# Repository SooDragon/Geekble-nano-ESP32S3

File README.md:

Geekble nano ESP32-S3
=============
Geekble nano ESP32-S3 문서에 오신것을 환영합니다

아두이노 IDE에서 쉽게 사용할 수 있는 Geekble nano를 통해 WiFi, Bluetooth, USB HID 기능을 여러분의 프로젝트에 구현할 수 있습니다

Geekble nano 핀맵
-------------

Geekble nano PinMap

Geekble nano 회로도
-------------

Geekble nano Schematic

Geekble nano 치수도
-------------

Geekble nano Dimension

Geekble nano Version Log
-------------
- Ver.1.0: 최초 공개 버전
- Ver.2.0: 3.3V Buck-Boost 회로에서 5V Buck-Boost + 3.3V 리니어 레귤레이터 구조로 변경
- Ver.2.2: 안테나 임피던스 매칭용 커페시터 C1, C2 값을 1.8pF에서 1.5pF으로 변경
- Ver.2.3: 안테나 임피던스 매칭용 커페시터 C1 값을 2pF으로, C2 값을 1pF으로 변경
- Ver.2.4:안테나 임피던스 매칭용 커페시터 C1 값을 1pF으로, C2 값을 2pF으로 변경
- Ver.2.5: 안테나 임피던스 매칭용 커페시터 C1 값을 1pF에서 1.2pF으로 변경

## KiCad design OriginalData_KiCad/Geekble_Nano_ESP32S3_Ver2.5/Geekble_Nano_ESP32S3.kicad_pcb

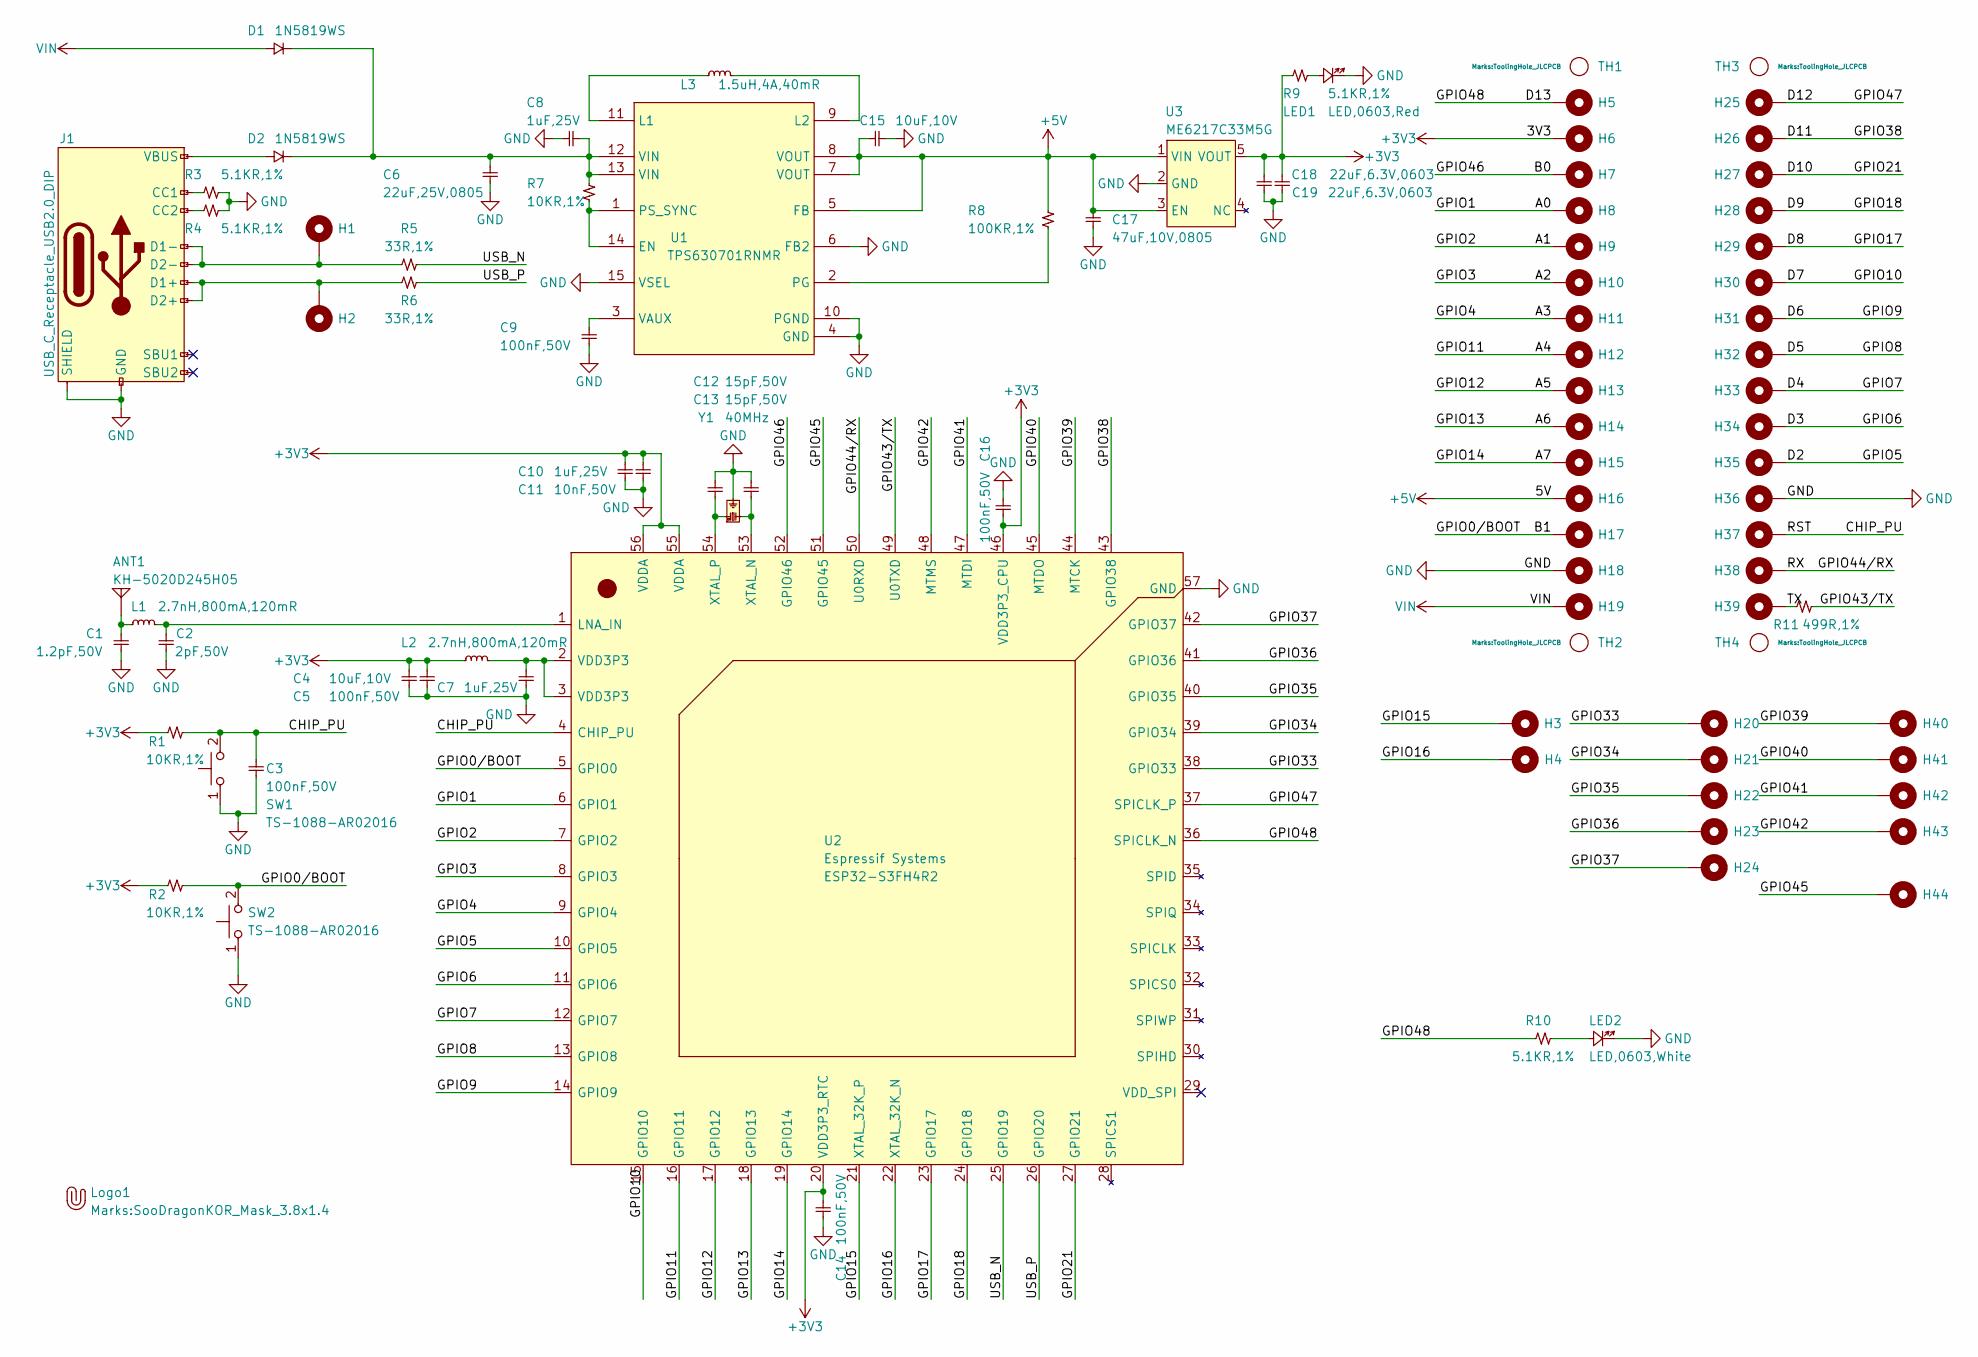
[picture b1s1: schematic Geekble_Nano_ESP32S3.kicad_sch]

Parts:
ANT1: KH-5020D245H05; ANT_5020; Manufacturer Part Number KH-5020D245H05; LCSC C45359218
C1: 1.2pF,50V; C_0402; Manufacturer Part Number CC0402BRNPO9BN1R2; LCSC C327292
C2: 2pF,50V; C_0402; Manufacturer Part Number CC0402BRNPO9BN2R0; LCSC C281756
C3, C5, C9, C14, C16: 100nF,50V; C_0402; Manufacturer Part Number CL05B104KB54PNC; LCSC C307331
C4, C15: 10uF,10V; C_0402; Manufacturer Part Number LDK105CBJ106MVLF; LCSC C386033
C6: 22uF,25V,0805; C_0805; Manufacturer Part Number CL21A226MAQNNNE; LCSC C45783
C7, C8, C10: 1uF,25V; C_0402; Manufacturer Part Number CL05A105KA5NQNC; LCSC C52923
C11: 10nF,50V; C_0402; Manufacturer Part Number CL05B103KB5NNNC; LCSC C15195
C12, C13: 15pF,50V; C_0402; Manufacturer Part Number 0402CG150J500NT; LCSC C1548
C17: 47uF,10V,0805; C_0805; Manufacturer Part Number GRM21BR61A476ME15L; LCSC C124129
C18, C19: 22uF,6.3V,0603; C_0603; Manufacturer Part Number CL10A226MQ8NRNC; LCSC C59461
D1, D2: 1N5819WS; SOD-323F; Manufacturer Part Number 1N5819WS; LCSC C191023
H1, H2, H3, H4, H20, H21, H22, H23, H24, H40, H41, H42, H43, H44: MountingHole_Pad; 1x1_1.0piPad_SMD
H5, H6, H7, H8, H9, H10, H11, H12, H13, H14, H15, H16, H17, H18, H19, H25, H26, H27, H28, H29, H30, H31, H32, H33, H34, H35, H36, H37, H38, H39: MountingHole_Pad; 1x1_P2.54_CastellatedPad
J1: USB_C_Receptacle_USB2.0_DIP; USB_DIP,8.94x7.3mm; Manufacturer Part Number TYPE-C-31-M-12; LCSC C165948
L1, L2: 2.7nH,800mA,120mR; L_0402; Manufacturer Part Number LQG15HS2N7S02D; LCSC C77108
L3: 1.5uH,4A,40mR; FTC201612S; Manufacturer Part Number FTC201612S1R5MBCA; LCSC C5832350
LED1: LED,0603,Red; LED_0603_Red; Manufacturer Part Number KT-0603R; LCSC C2286
LED2: LED,0603,White; LED_0603_White; LCSC C2290
Logo1: Geekble_Logo; SooDragonKOR_Mask_3.8x1.4
R1, R2, R7: 10KR,1%; R_0402; Manufacturer Part Number 0402WGF1002TCE; LCSC C25744
R3, R4, R9, R10: 5.1KR,1%; R_0402; Manufacturer Part Number 0402WGF5101TCE; LCSC C25905
R5, R6: 33R,1%; R_0402; Manufacturer Part Number 0402WGF330JTCE; LCSC C25105
R8: 100KR,1%; R_0402; Manufacturer Part Number 0402WGF1003TCE; LCSC C25741
R11: 499R,1%; R_0402; Manufacturer Part Number 0402WGF4990TCE; LCSC C4125
SW1, SW2: TS-1088-AR02016; TS-1088-AR020; Manufacturer Part Number TS-1088-AR02016; LCSC C720477
TH1, TH2, TH3, TH4: ToolingHole; ToolingHole_JLCPCB
U1: TPS630701RNMR; RNM0015A; Manufacturer Part Number TPS630701RNMR; LCSC C2876599
U2: ESP32-S3FH4R2; QFN-56-1EP_7x7mm_P0.4mm_EP5.6x5.6mm; Manufacturer Part Number ESP32-S3FH4R2; LCSC C3013940
U3: ME6217C33M5G; SOT-23-5; Manufacturer Part Number ME6217C33M5G; LCSC C427602
Y1: 40MHz; SMD-3225_4P; Manufacturer Part Number X322540MPB4SI; LCSC C9010

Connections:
+3V3: C4.2, C5.2, C10.2, C11.2, C14.2, C16.2, C18.2, C19.2, H6.1, L2.1, R1.1, R2.1, R9.1, U2.20 (VDD3P3_RTC), U2.46 (VDD3P3_CPU), U2.55 (VDDA), U2.56 (VDDA), U3.5 (VOUT)
+5V: C15.2, C17.2, H16.1, R8.2, U1.5 (FB), U1.7 (VOUT), U1.8 (VOUT), U3.1 (VIN), U3.3 (EN)
/A0: H8.1, U2.6 (GPIO1)
/A1: H9.1, U2.7 (GPIO2)
/A2: H10.1, U2.8 (GPIO3)
/A3: H11.1, U2.9 (GPIO4)
/A4: H12.1, U2.16 (GPIO11)
/A5: H13.1, U2.17 (GPIO12)
/A6: H14.1, U2.18 (GPIO13)
/A7: H15.1, U2.19 (GPIO14)
/B0: H7.1, U2.52 (GPIO46)
/B1: H17.1, R2.2, SW2.2 (B), U2.5 (GPIO0)
/CHIP_PU: C3.2, H37.1, R1.2, SW1.2 (B), U2.4 (CHIP_PU)
/D2: H35.1, U2.10 (GPIO5)
/D3: H34.1, U2.11 (GPIO6)
/D4: H33.1, U2.12 (GPIO7)
/D5: H32.1, U2.13 (GPIO8)
/D6: H31.1, U2.14 (GPIO9)
/D7: H30.1, U2.15 (GPIO10)
/D8: H29.1, U2.23 (GPIO17)
/D9: H28.1, U2.24 (GPIO18)
/D10: H27.1, U2.27 (GPIO21)
/D11: H26.1, U2.43 (GPIO38)
/D12: H25.1, U2.37 (SPICLK_P)
/D13: H5.1, R10.2, U2.36 (SPICLK_N)
/GPIO15: H3.1, U2.21 (XTAL_32K_P)
/GPIO16: H4.1, U2.22 (XTAL_32K_N)
/GPIO33: H20.1, U2.38 (GPIO33)
/GPIO34: H21.1, U2.39 (GPIO34)
/GPIO35: H22.1, U2.40 (GPIO35)
/GPIO36: H23.1, U2.41 (GPIO36)
/GPIO37: H24.1, U2.42 (GPIO37)
/GPIO39: H40.1, U2.44 (MTCK)
/GPIO40: H41.1, U2.45 (MTDO)
/GPIO41: H42.1, U2.47 (MTDI)
/GPIO42: H43.1, U2.48 (MTMS)
/GPIO43/TX: R11.1, U2.49 (U0TXD)
/GPIO44/RX: H38.1, U2.50 (U0RXD)
/GPIO45: H44.1, U2.51 (GPIO45)
/TX: H39.1, R11.2
/USB_N: R5.2, U2.25 (GPIO19)
/USB_P: R6.2, U2.26 (GPIO20)
GND: C1.1, C2.1, C3.1, C4.1, C5.1, C6.1, C7.1, C8.1, C9.1, C10.1, C11.1, C12.1, C13.1, C14.1, C15.1, C16.1, C17.1, C18.1, C19.1, H18.1, H36.1, J1.A1B12 (GND), J1.B1A12 (GND), J1.S1 (SHIELD), J1.S2 (SHIELD), J1.S3 (SHIELD), J1.S4 (SHIELD), LED1.C, LED2.C, R3.2, R4.2, SW1.1 (A), SW2.1 (A), U1.4 (GND), U1.6 (FB2), U1.10 (PGND), U1.15 (VSEL), U2.57 (GND), U3.2 (GND), Y1.2 (GND), Y1.4 (GND)
unnamed: ANT1.Feed, C1.2, L1.1
unnamed: C6.2, C8.2, D1.C, D2.C, R7.2, U1.12 (VIN), U1.13 (VIN)
unnamed: C7.2, L2.2, U2.2 (VDD3P3), U2.3 (VDD3P3)
unnamed: D2.A, J1.A4B9 (VBUS), J1.B4A9 (VBUS)
unnamed: J1.A5 (CC1), R3.1
unnamed: J1.B5 (CC2), R4.1
unnamed: H2.1, J1.A6 (D1+), J1.B6 (D2+), R6.1
unnamed: H1.1, J1.A7 (D1-), J1.B7 (D2-), R5.1
unnamed: LED1.A, R9.2
unnamed: LED2.A, R10.1
unnamed: R7.1, U1.1 (PS_SYNC), U1.14 (EN)
unnamed: L3.1, U1.11 (L1)
unnamed: L3.2, U1.9 (L2)
unnamed: R8.1, U1.2 (PG)
unnamed: C9.2, U1.3 (VAUX)
unnamed: C2.2, L1.2, U2.1 (LNA_IN)
unnamed: C13.2, U2.53 (XTAL_N), Y1.3 (OSC2)
unnamed: C12.2, U2.54 (XTAL_P), Y1.1 (OSC1)
VIN: D1.A, H19.1

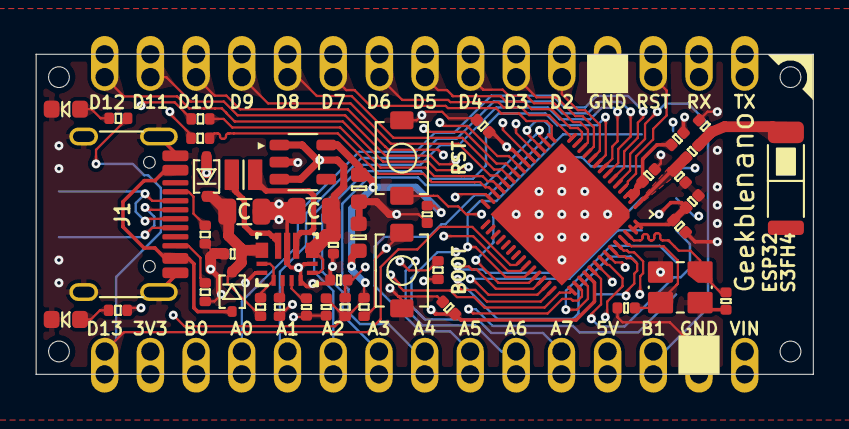
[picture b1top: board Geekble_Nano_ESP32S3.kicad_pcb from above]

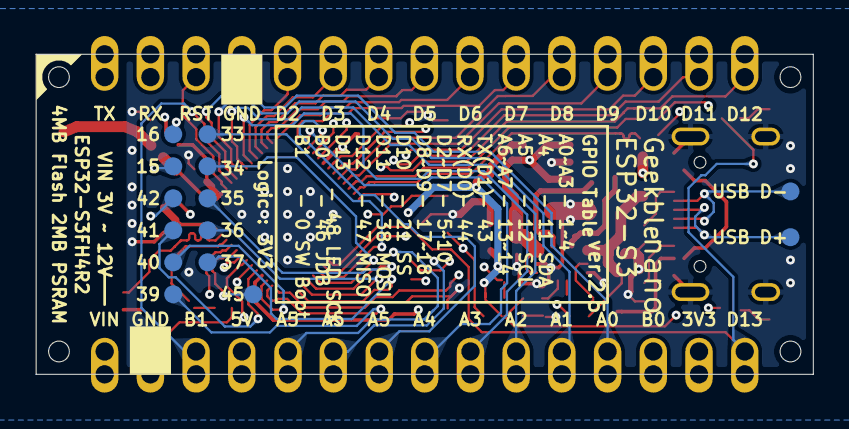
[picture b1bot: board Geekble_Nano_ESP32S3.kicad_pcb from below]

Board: 4 copper layers, 43.2 x 17.8 mm, 94 parts (14 on the bottom side), 62 nets.

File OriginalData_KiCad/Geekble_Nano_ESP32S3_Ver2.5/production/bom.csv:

Designator,Footprint,Quantity,Value,LCSC Part #
ANT1,ANT_5020,1,KH-5020D245H05,C45359218
C1,C_0402,1,"1.2pF,50V",C327292
"C10, C7, C8",C_0402,3,"1uF,25V",C52923
C11,C_0402,1,"10nF,50V",C15195
"C12, C13",C_0402,2,"15pF,50V",C1548
"C14, C16, C3, C5, C9",C_0402,5,"100nF,50V",C307331
"C15, C4",C_0402,2,"10uF,10V",C386033
C17,C_0805,1,"47uF,10V,0805",C124129
"C18, C19",C_0603,2,"22uF,6.3V,0603",C59461
C2,C_0402,1,"2pF,50V",C281756
C6,C_0805,1,"22uF,25V,0805",C45783
"D1, D2",SOD-323F,2,1N5819WS,C191023
"H1, H2, H20, H21, H22, H23, H24, H3, H4, H40, H41, H42, H43, H44",1x1_1.0piPad_SMD,14,MountingHole_Pad,
"H10, H11, H12, H13, H14, H15, H16, H17, H18, H19, H25, H26, H27, H28, H29, H30, H31, H32, H33, H34, H35, H36, H37, H38, H39, H5, H6, H7, H8, H9",1x1_P2.54_CastellatedPad,30,MountingHole_Pad,
J1,"USB_DIP,8.94x7.3mm",1,USB_C_Receptacle_USB2.0_DIP,C165948
"L1, L2",L_0402,2,"2.7nH,800mA,120mR",C77108
L3,FTC201612S,1,"1.5uH,4A,40mR",C5832350
LED1,LED_0603_Red,1,"LED,0603,Red",C2286
LED2,LED_0603_White,1,"LED,0603,White",C2290
LOGO1,SooDragonKOR_Mask_3.8x1.4,1,Geekble_Logo,
"R1, R2, R7",R_0402,3,"10KR,1%",C25744
"R10, R3, R4, R9",R_0402,4,"5.1KR,1%",C25905
R11,R_0402,1,"499R,1%",C4125
"R5, R6",R_0402,2,"33R,1%",C25105
R8,R_0402,1,"100KR,1%",C25741
"SW1, SW2",TS-1088-AR020,2,TS-1088-AR02016,C720477
"TH1, TH2, TH3, TH4",ToolingHole_JLCPCB,4,ToolingHole,
U1,RNM0015A,1,TPS630701RNMR,C2876599
U2,QFN-56-1EP_7x7mm_P0.4mm_EP5.6x5.6mm,1,ESP32-S3FH4R2,C3013940
U3,SOT-23-5,1,ME6217C33M5G,C427602
Y1,SMD-3225_4P,1,40MHz,C9010

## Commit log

2025-02-23 1.0
    1.0 data
2025-02-23 Pic
    Pic
2025-03-02 Ver.2.0
2025-03-03 2.0
    2.0
2025-04-29 Ver2.2
2025-06-16 ud
    ud
2025-07-27 Ver.2.5
    Ver.2.5
